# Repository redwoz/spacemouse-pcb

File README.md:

# spacemouse-pcb

Wooohooo a new package!

https://www.printables.com/model/926332-smaller-spacemouse-with-hall-effect-joysticks-pcb

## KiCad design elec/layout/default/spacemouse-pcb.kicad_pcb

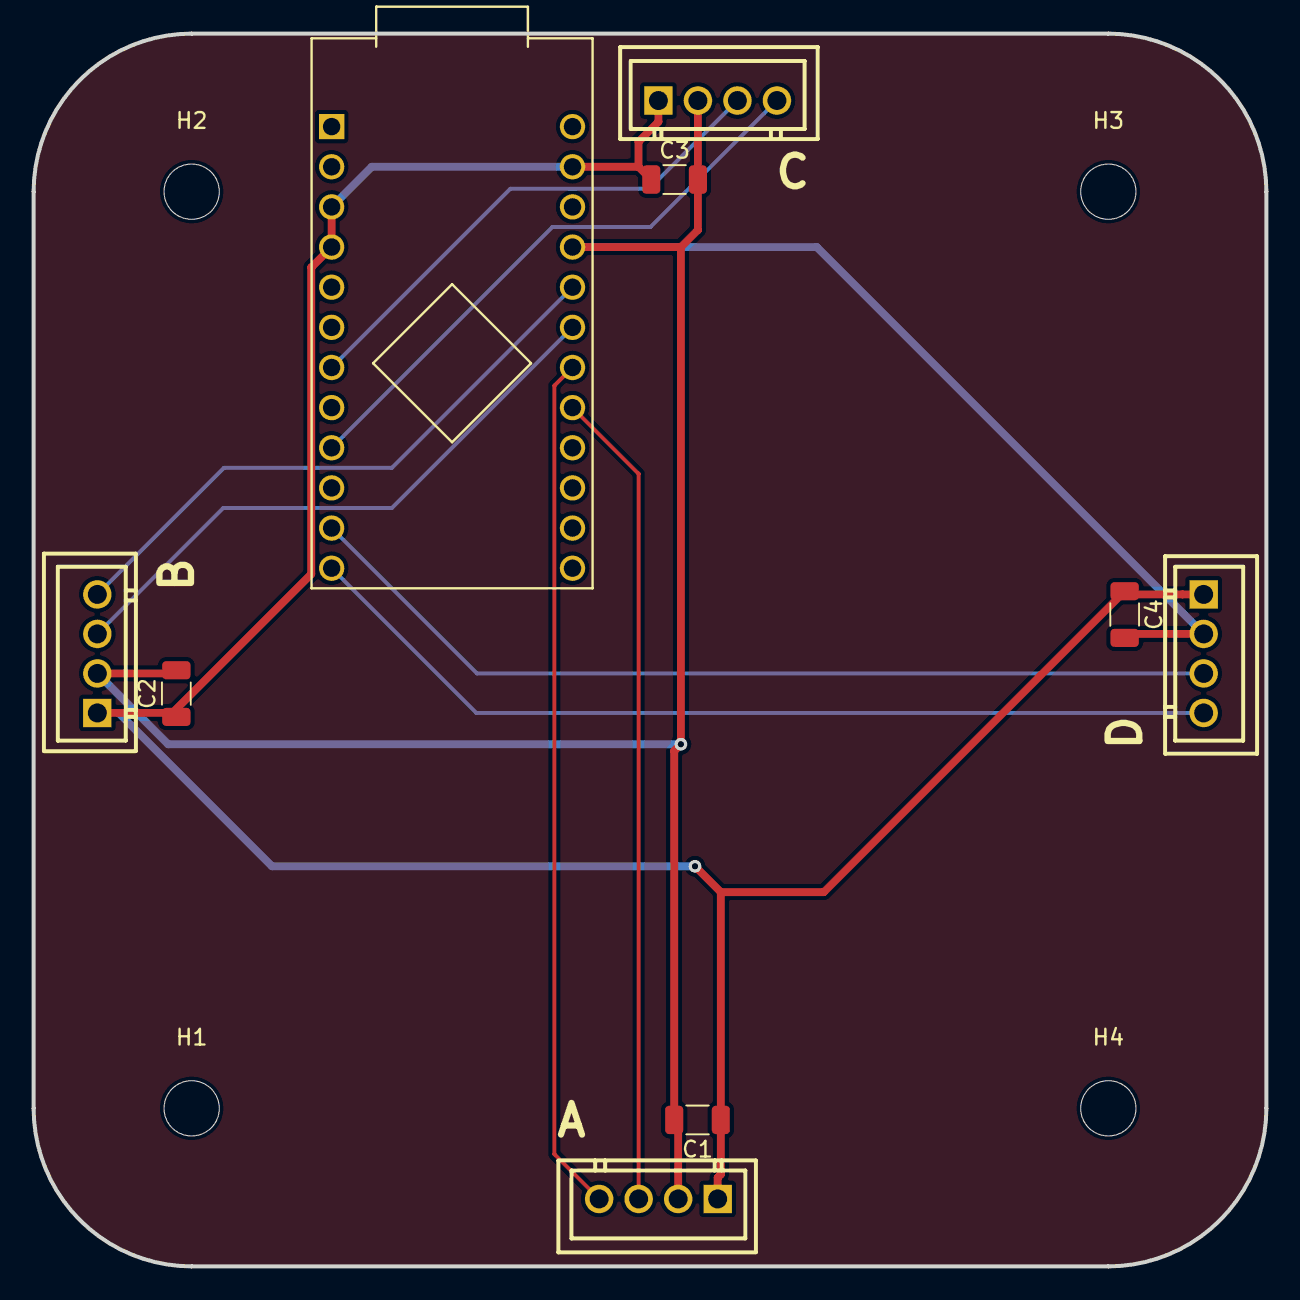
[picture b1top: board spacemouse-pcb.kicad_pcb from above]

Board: 2 copper layers, 78.0 x 78.0 mm, 13 parts (0 on the bottom side), 10 nets.

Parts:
A: CONN-TH_4P-P2.50_XH-4A
B: CONN-TH_4P-P2.50_XH-4A
C: CONN-TH_4P-P2.50_XH-4A
C1, C2, C3, C4: 50V 100nF X7R ±10% 1206 Multilayer Ceramic Capaci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; C1206
D: CONN-TH_4P-P2.50_XH-4A
H1, H2, H3, H4: MountingHole_3.5mm
U1: ProMicro

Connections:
a0: A.3, U1.17
a1: A.4, U1.18
a2: B.3, U1.19
a3: B.4, U1.20
a6: C.3, U1.7
a7: C.4, U1.9
a8: D.3, U1.11
a9: D.4, U1.12
gnd: A.1, B.1, C.1, C1.1, C2.1, C3.1, C4.1, D.1, U1.3, U1.4, U1.23
vcc: A.2, B.2, C.2, C1.2, C2.2, C3.2, C4.2, D.2, U1.21

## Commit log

2024-08-05 Configure project
2024-08-05 initial setup
2024-08-06 promicrofp
2024-08-06 start
2024-08-09 basic complete
2024-08-20 fix swapped XYs, cleaner labels
